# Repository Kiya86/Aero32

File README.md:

# Aero32

<h4 align="center">
A custom STM32N6-based AI vision module!
</h4>

<div align="center">

</div>

<p align="center">
  <a href="#key-features">Key Features</a> •
  <a href="#purpose">Purpose</a> •
  <a href="#pcb">PCB</a> •
  <a href="#main-components">Main Components</a> •
  <a href="#communication-interfaces">Communication Interfaces</a> •
  <a href="#power-architecture">Power System</a> •
  <a href="#bom">BOM</a> 
</p>

## Key Features

- **STM32N657X0H3Q** - Neural-ART accelerator that is used alongside the STM32N6 MCU
- **15-Pin CSI FPC Connector** - Camera sensor interface
- **MT35XU256ABA1G12** - 256 Mbit Octal SPI NOR Flash for either firmware or data 
- **IS66WVO32M8DALL** - 256 Mbit PSRAM for working memory
- **2× UART Ports** - Serial breakout headers
- **2× I2C Ports** - Two-wire serial communication breakout headers
- **1× SPI Port** - High-speed peripheral interface breakout
- **48 MHz & 32.768 kHz Crystals** - System clock and low power RTC
- **XT30 Battery Input** - 3S–4S LiPo input
- **5× Status LEDs** - 3 green + 2 red for power and debug feedback
- **Input OR** - TPS2121 power multiplexer for safe dual-source power switching

## Purpose

Aero32 is a small and compact AI vision board designed to serve as a node for drones or other flight hardware. The board offloads computer vision and processing from the external processing, communicating the results over UART, I2C, or SPI.

The STM32N6's Neural Processing Unit (NPU) allows anomaly detection, human recognition, and other advanced recognition directly on the board without AI hardware or wifi.

## PCB

Designed in **KiCad** and manufactured through **JLCPCB** (soon). The board uses a **6-layer PCB stackup** to allow for a reduction of EMI and signal interference. 

### Schematic

## Main Components

| Category | Component | Description |
|---|---|---|
| Microcontroller | STM32N657X0H3Q | STM32N6 with NPU |
| NOR Flash | MT35XU256ABA1G12-0AUT | 256 Mbit Octal SPI Flash (Micron) |
| PSRAM | IS66WVO32M8DALL-200BLI | 256 Mbit Pseudo-SRAM (ISSI) |
| Camera Connector | XF3M(1)-1515-1B | 15-Pin 1mm Pitch FPC (Omron) |
| Main Buck Regulator | LM61495Q5RPHRQ1 | 3–36V 10A Automotive Buck (TI) |
| Aux Buck (3A) | AP3441LSHE-7B | 2.7–5.5V 3A Adjustable Buck |
| Aux Buck (3A) | TPS62088YFPR | 2.4–5.5V 3A Adjustable Buck (TI) |
| Fixed 3.3V Buck | TPS560430X3FDBVR | 4–36V 600mA 3.3V Fixed Buck (TI) |
| 1.8V LDO (×2) | ETA5055V180DD1E | 1.8V 500mA LDO |
| 3.3V LDO | ETA5055V330DD1E | 3.3V 500mA LDO |
| Power Mux | TPS2121RUXR | ORing Power Multiplexer (TI) |
| USB ESD | TPD2E001DRYR | 2-Channel USB ESD Protection (TI) |
| USB Connector | HC-TYPE-C-16P-01A-G | USB Type-C 16P 3A Female |
| Power Input | XT30PW-M | XT30 Male 15A Connector |
| System Crystal | SX0B48.000F0810F30 | 48 MHz ±10ppm Crystal |
| RTC Crystal | NX2012SA 32.768K | 32.768 kHz ±20ppm Crystal |
| Boot / Reset | K2-1808SN-A4SW | SPST Tactile Switch (×2) |
| Status LEDs | KT-0603G / KT-0603R | Green (×3) / Red (×2) 0603 LEDs |
| TVS Diode | LESD5D5.0CT1G | 150W Bidirectional TVS 5V |

## Communication Interfaces

### UART (×2)
Two independent UART breakout ports via 2-pin JST ZH 1.5mm connectors.

### I2C (×2)
Two I2C ports broken out via JST ZH 1.5mm connectors.

### SPI (×1)
One SPI port available for high-speed peripheral communication.

### Camera (CSI)
A 15-pin 1mm pitch FPC connector (Omron XF3M) provides the camera sensor interface.

## Power Architecture

Aero32 supports dual power inputs (USB-C and XT30 battery) with automatic source switching via the TPS2121 power mux.

## BOM

The full Bill of Materials is available in [`Aero32_BOM.csv`](./PCB/Aero32_BOM.csv), formatted for direct JLCPCB assembly upload.

JLCPCB Quote

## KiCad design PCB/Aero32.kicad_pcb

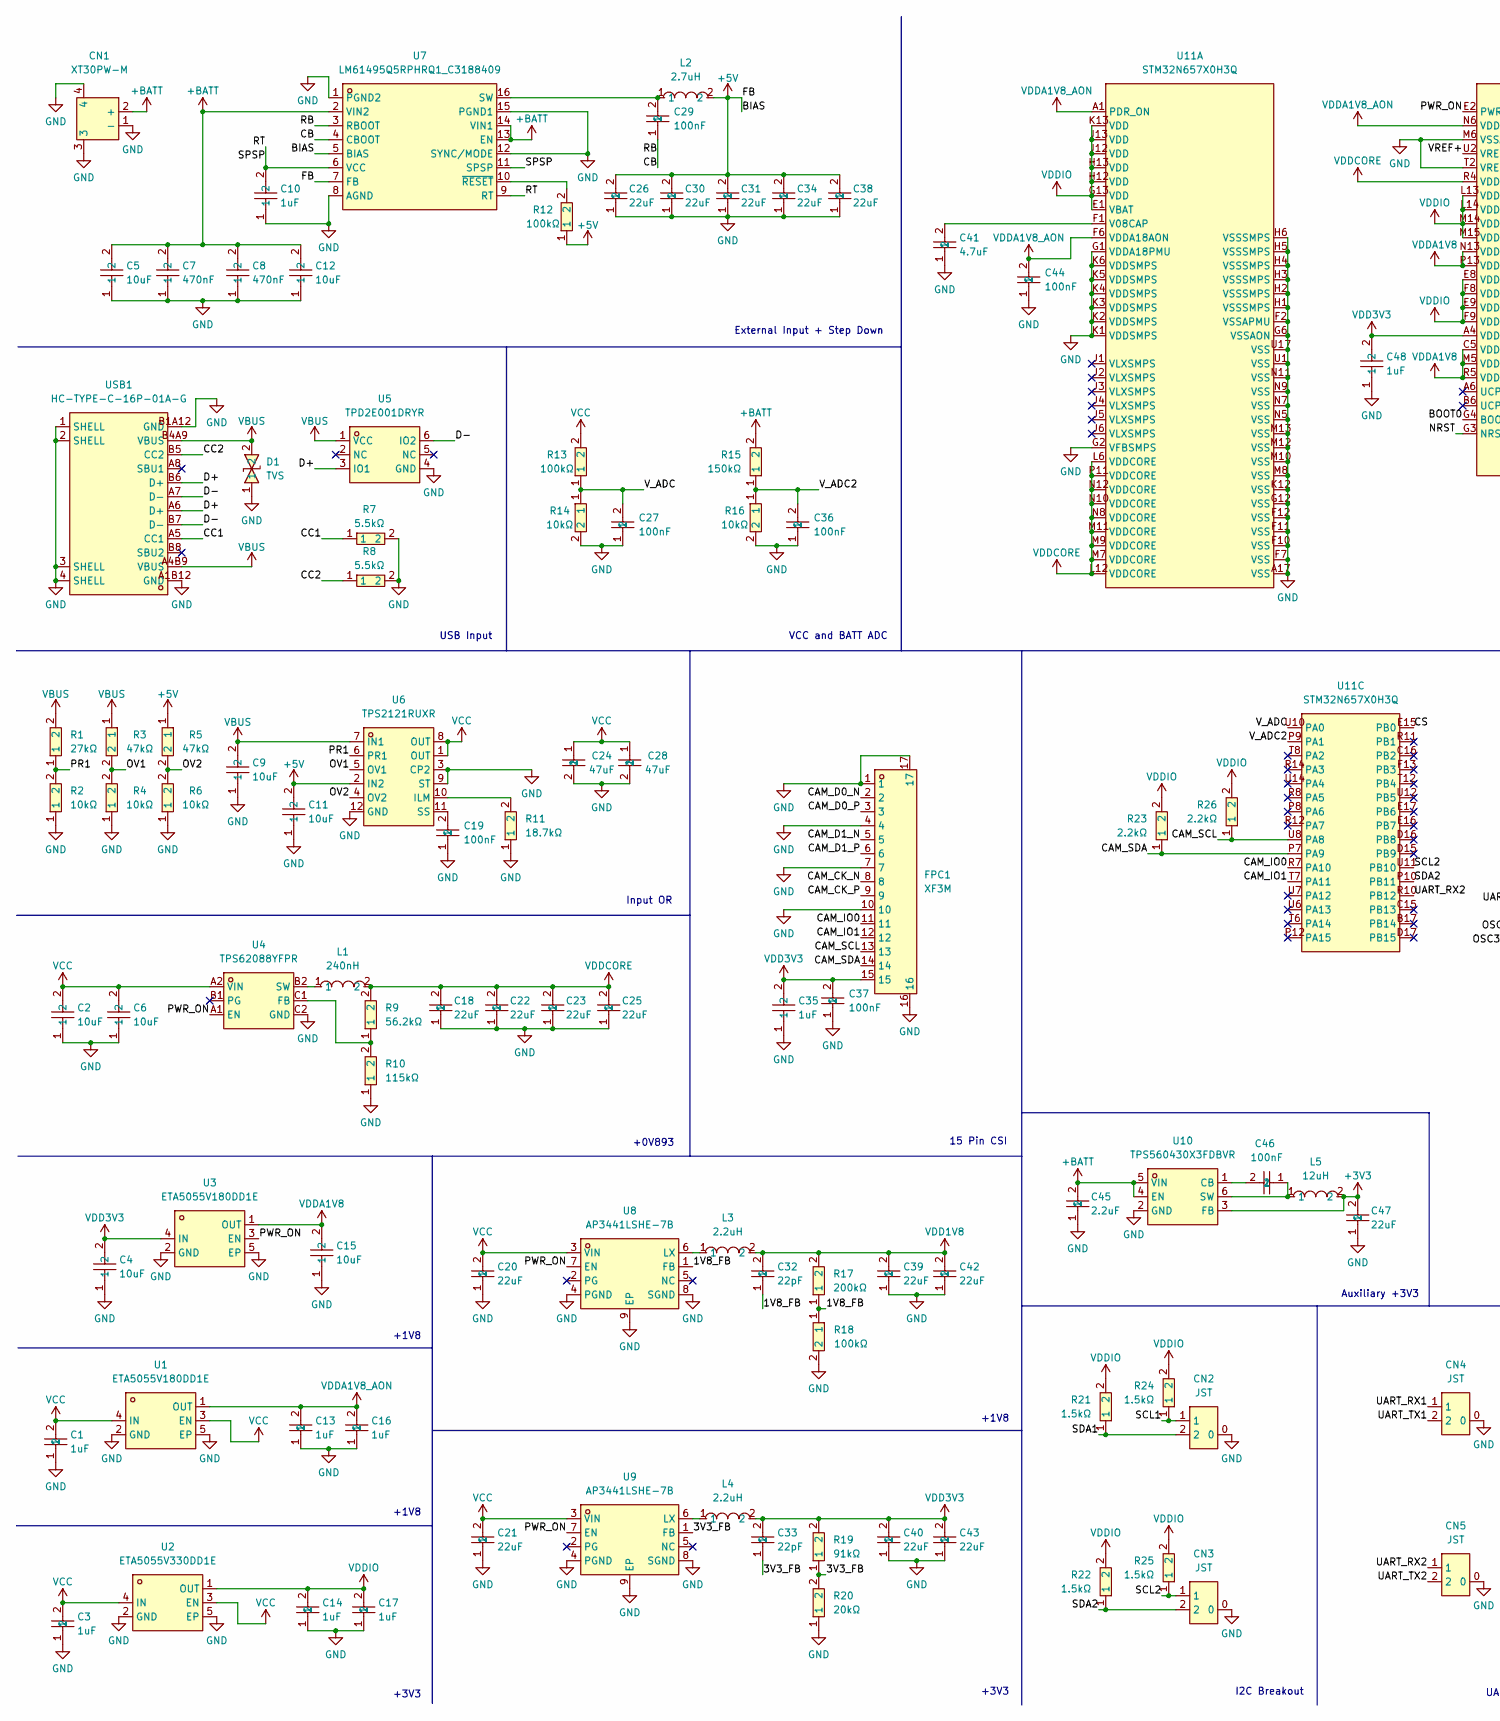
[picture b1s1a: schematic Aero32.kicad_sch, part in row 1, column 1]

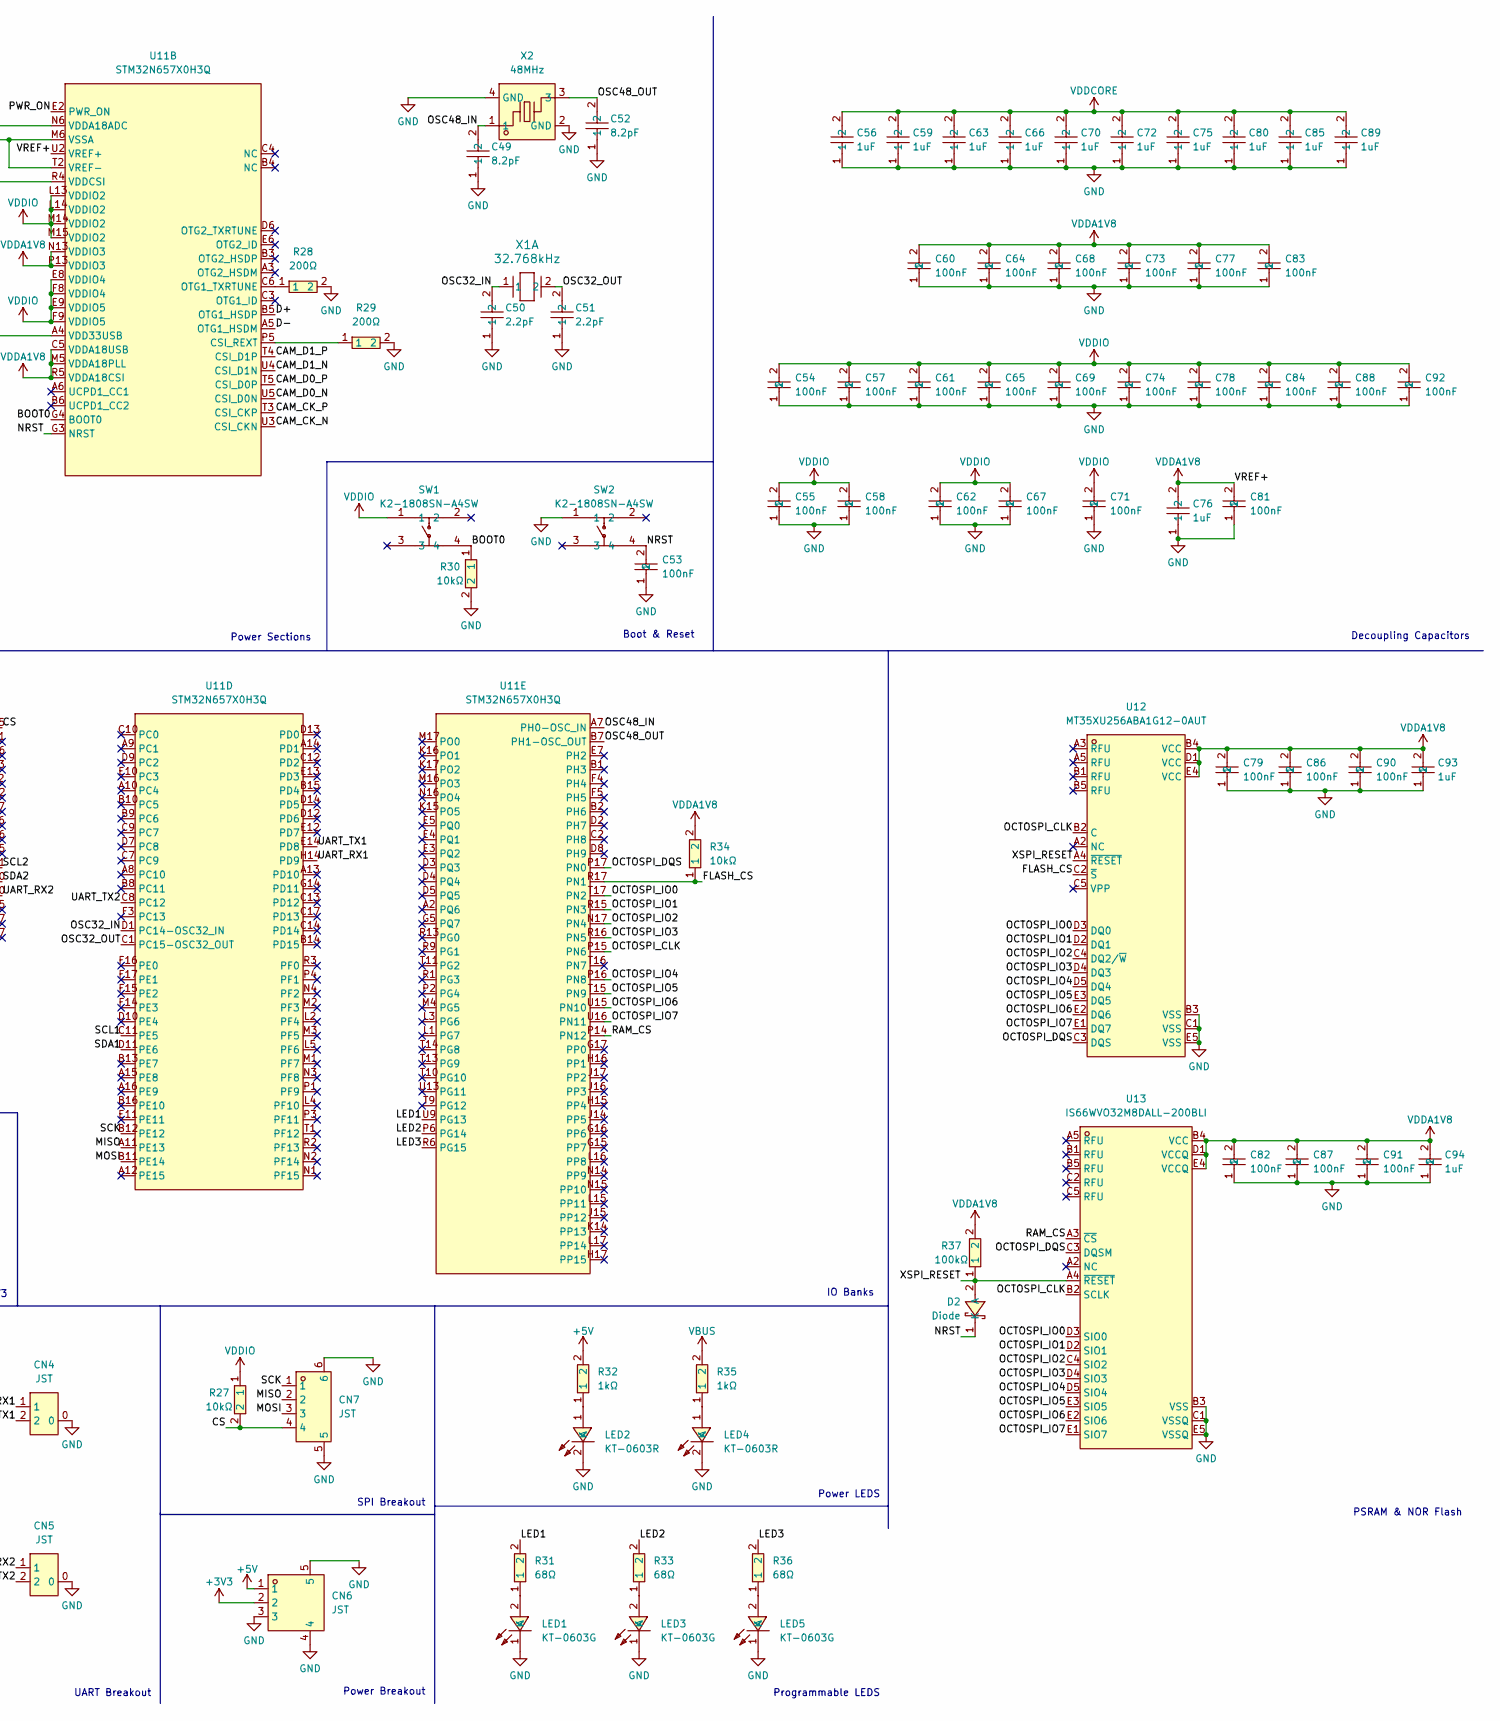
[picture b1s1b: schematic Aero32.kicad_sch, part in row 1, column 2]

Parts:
C1, C3, C13, C14, C16, C17, C93, C94: 1uF; C0603; MPN CL10A105KO8NNNC; LCSC Part C1592
C2, C4, C5, C6, C9, C11, C12, C15: 10uF; C0805; MPN GRM21BR61H106KE43L; LCSC Part C440198
C7, C8: 470nF; C0603; MPN CC0603KRX7R9BB474; LCSC Part C513577
C10, C35, C48, C56, C59, C63, C66, C70, C72, C75, C76, C80, C85, C89: 1uF; C0603; MPN CL10A105KB8NNNC; LCSC Part C15849
C18, C20, C21, C22, C23, C25, C26, C30, C31, C34, C38, C39, C40, C42, C43, C47: 22uF; C0805; MPN C2012X5R1A226KT000N; LCSC Part C76634
C19, C27, C29, C36, C37, C44, C46, C53, C54, C55, C57, C58, C60, C61, C62, C64, C65, C67, C68, C69, C71, C73, C74, C77, C78, C79, C81, C82, C83, C84, C86, C87, C88, C90, C91, C92: 100nF; C0603; MPN GRM188R71C104KA01D; LCSC Part C45000
C24, C28: 47uF; C1210; MPN GRM32ER71A476KE15L; LCSC Part C84494
C32, C33: 22pF; C0402; MPN 0402CG220J500NT; LCSC Part C1555
C41: 4.7uF; C0603; MPN CL10A475KP8NNNC; LCSC Part C1705
C45: 2.2uF; C0603; MPN CL10A225KP8NNNC; LCSC Part C1607
C49, C52: 8.2pF; C0402; MPN CC0402CRNPO9BN8R2; LCSC Part C260529
C50, C51: 2.2pF; C0402; MPN GJM1555C1H2R2WB01D; LCSC Part C88887
CN1: XT30PW-M; CONN-TH_XT30PW-M; MPN XT30PW-M30.G.Y; LCSC Part C431092
CN2, CN3, CN4, CN5: JST; CONN-SMD_S2B-ZR-SM4A; MPN S2B-ZR-SM4A-TF(LF)(SN); LCSC Part C265329
CN6: JST; CONN-TH_S3B-ZR-SM4A-TF-LF-SN; MPN S3B-ZR-SM4A-TF(LF)(SN); LCSC Part C72591
CN7: JST; CONN-SMD_4P-P1.50_S4B-ZR-SM4A-TF-LF-SN; MPN S4B-ZR-SM4A-TF(LF)(SN); LCSC Part C485354
D1: TVS; SOD-523_L1.2-W0.8-LS1.6-BI; MPN LESD5D5.0CT1G; LCSC Part C383211
D2: Diode; DSN2_L1.0-W0.6-RD; MPN NSR05F30NXT5G; LCSC Part C604339
FPC1: XF3M; FPC-SMD_XF3M-1-1515-1B; MPN XF3M(1)-1515-1B; LCSC Part C6036307
L1: 240nH; IND-SMD_L3.0-W3.0_MAI3015S; MPN MAI3015S-R24MT; LCSC Part C520265
L2: 2.7uH; IND-SMD_DH0630H-1R5M; MPN DH0630H-2R7M; LCSC Part C41407066
L3, L4: 2.2uH; IND-SMD_L4.5-W4.1_GSSM0420; MPN SL0420-2R2M; LCSC Part C22463806
L5: 12uH; IND-SMD_L4.8-W4.8; MPN LPS5030-123MRC; LCSC Part C22385343
LED1, LED3, LED5: KT-0603G; LED0603-RD; MPN KT-0603G; LCSC Part C12624
LED2, LED4: KT-0603R; LED-SMD_L1.6-W0.8-R-RD; MPN KT-0603R; LCSC Part C2286
R1: 27kΩ; R0603; MPN 0603WAF2702T5E; LCSC Part C22967
R2, R4, R6, R34: 10kΩ; R0603; MPN 0603WAF1002T5E; LCSC Part C25804
R3, R5: 47kΩ; R0603; MPN 0603WAF4702T5E; LCSC Part C25819
R7, R8: 5.5kΩ; R0805; MPN RMC08055.1K1%N; LCSC Part C269748
R9: 56.2kΩ; R0603; MPN 0603WAF5622T5E; LCSC Part C23080
R10: 115kΩ; R0603; MPN 0603WAF1153T5E; LCSC Part C22783
R11: 18.7kΩ; R0603; MPN 0603WAF1872T5E; LCSC Part C22893
R12, R13, R18, R37: 100kΩ; R0603; MPN RC0603FR-07100KL; LCSC Part C14675
R14, R16, R27, R30: 10kΩ; R0603; MPN 0603WAJ0103T5E; LCSC Part C15401
R15: 150kΩ; R0603; MPN 0603WAF1503T5E; LCSC Part C22807
R17: 200kΩ; R0603; MPN 0603WAF2003T5E; LCSC Part C25811
R19: 91kΩ; R0603; MPN 0603WAF9102T5E; LCSC Part C23265
R20: 20kΩ; R0603; MPN 0603WAF2002T5E; LCSC Part C4184
R21, R22, R24, R25: 1.5kΩ; R0402; MPN 0402WGF1501TCE; LCSC Part C25867
R23, R26: 2.2kΩ; R0402; MPN 0402WGF2201TCE; LCSC Part C25879
R28, R29: 200Ω; R0603; MPN 0603WAF2000T5E; LCSC Part C8218
R31, R33, R36: 68Ω; R0402; MPN 0402WGJ0680TCE; LCSC Part C25178
R32, R35: 1kΩ; R0402; MPN 0402WGF1001TCE; LCSC Part C11702
SW1, SW2: K2-1808SN-A4SW; KEY-SMD_4P-L4.2-W3.2-P2.20-LS5.1-TL; MPN K2-1808SN-A4SW-01; LCSC Part C92589
U1, U3: ETA5055V180DD1E; DFN-4_L1.0-W1.0-P0.65-BL-EP; MPN ETA5055V180DD1E; LCSC Part C5776774
U2: ETA5055V330DD1E; XDFN-4_L1.0-W1.0-P0.65-BL-EP; MPN ETA5055V330DD1E; LCSC Part C22466949
U4: TPS62088YFPR; DSBGA-6_L0.8-W1.2-P0.40-R3-C2-TL; MPN TPS62088YFPR; LCSC Part C575572
U5: TPD2E001DRYR; SON-6_L1.5-W1.0-P0.50-BL; MPN TPD2E001DRYR; LCSC Part C379992
U6: TPS2121RUXR; VQFN-HR-12_L2.5-W2.0-P0.50-BL; MPN TPS2121RUXR; LCSC Part C485916
U7: LM61495Q5RPHRQ1_C3188409; VQFN-16_L4.5-W3.5-P0.50-TL_TI_RPH; MPN LM61495Q5RPHRQ1; LCSC Part C3188409
U8, U9: AP3441LSHE-7B; DFN-8_L2.0-W2.0-P0.50-BL-EP1.7; MPN AP3441LSHE-7B; LCSC Part C2072094
U10: TPS560430X3FDBVR; SOT-23-6_L2.9-W1.6-P0.95-LS2.8-BR; MPN TPS560430X3FDBVR; LCSC Part C2071721
U11: STM32N657X0H3Q; BGA-264_L14.0-W14.0-STM32N657X0H3Q; MPN STM32N657X0H3Q; LCSC Part C42418080
U12: MT35XU256ABA1G12-0AUT; T-PBGA-24_L8.0-W6.0-P1.00-TL_MICRON_12; MPN MT35XU256ABA1G12-0AUT; LCSC Part C7235747
U13: IS66WVO32M8DALL-200BLI; TFBGA-24_L8.0-W6.0-P1.00-TL_MX25UW25645GXDI00; MPN IS66WVO32M8DALL-200BLI; LCSC Part C17535354
USB1: HC-TYPE-C-16P-01A-G; USB-C-SMD_G-SWITCH_GT-USB-7010EN; MPN HC-TYPE-C-16P-01A-G; LCSC Part C2997435
X1: 32.768kHz; XTAL_NX2012SA_NDK
X2: 48MHz; CRYSTAL-SMD_4P-L1.6-W1.2-BL; MPN SX0B48.000F0810F30; LCSC Part C7301928

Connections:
+3V3: C47.2, CN6.2, L5.2, U10.3 (FB)
+5V: C11.2, C26.2, C30.2, C31.2, C34.2, C38.2, CN6.1, L2.2, R5.1, R12.1, R32.2, U6.2 (IN2), U7.5 (BIAS), U7.7 (FB)
+BATT: C5.2, C7.2, C8.2, C12.2, C45.2, CN1.2 (+), R15.2, U7.2 (VIN2), U7.13 (EN), U7.14 (VIN1), U10.4 (EN), U10.5 (VIN)
/3V3_FB: C33.1, R19.1, R20.2, U9.1 (FB)
/BOOT0: R30.1, SW1.4, U11.G4 (BOOT0)
/CAM_CK_N: FPC1.8, U11.U3 (CSI_CKN)
/CAM_CK_P: FPC1.9, U11.T3 (CSI_CKP)
/CAM_D0_N: FPC1.2, U11.U5 (CSI_D0N)
/CAM_D0_P: FPC1.3, U11.T5 (CSI_D0P)
/CAM_D1_N: FPC1.5, U11.U4 (CSI_D1N)
/CAM_D1_P: FPC1.6, U11.T4 (CSI_D1P)
/CAM_IO0: FPC1.11, U11.R7 (PA10)
/CAM_IO1: FPC1.12, U11.T7 (PA11)
/CAM_SCL: FPC1.13, R26.1, U11.U8 (PA8)
/CAM_SDA: FPC1.14, R23.1, U11.P7 (PA9)
/CB: C29.1, U7.3 (RBOOT), U7.4 (CBOOT)
/CC1: R7.1, USB1.A5 (CC1)
/CC2: R8.1, USB1.B5 (CC2)
/CS: CN7.4, R27.2, U11.E15 (PB0)
/D+: U5.3 (IO1), U11.B5 (OTG1_HSDP), USB1.A6 (D+), USB1.B6 (D+)
/D-: U5.6 (IO2), U11.A5 (OTG1_HSDM), USB1.A7 (D-), USB1.B7 (D-)
/FLASH_CS: R34.1, U11.R17 (PN1), U12.C2 (~S)
/LED1: R31.2, U11.U9 (PG13)
/LED2: R33.2, U11.P6 (PG14)
/LED3: R36.2, U11.R6 (PG15)
/MISO: CN7.2, U11.A11 (PE13)
/MOSI: CN7.3, U11.B11 (PE14)
/NRST: C53.2, D2.1 (K), SW2.4, U11.G3 (NRST)
/OCTOSPI_CLK: U11.P15 (PN6), U12.B2 (C), U13.B2 (SCLK)
/OCTOSPI_DQS: U11.P17 (PN0), U12.C3 (DQS), U13.C3 (DQSM)
/OCTOSPI_IO0: U11.T17 (PN2), U12.D3 (DQ0), U13.D3 (SIO0)
/OCTOSPI_IO1: U11.R15 (PN3), U12.D2 (DQ1), U13.D2 (SIO1)
/OCTOSPI_IO2: U11.N17 (PN4), U12.C4 (DQ2/~W), U13.C4 (SIO2)
/OCTOSPI_IO3: U11.R16 (PN5), U12.D4 (DQ3), U13.D4 (SIO3)
/OCTOSPI_IO4: U11.P16 (PN8), U12.D5 (DQ4), U13.D5 (SIO4)
/OCTOSPI_IO5: U11.T15 (PN9), U12.E3 (DQ5), U13.E3 (SIO5)
/OCTOSPI_IO6: U11.U15 (PN10), U12.E2 (DQ6), U13.E2 (SIO6)
/OCTOSPI_IO7: U11.U16 (PN11), U12.E1 (DQ7), U13.E1 (SIO7)
/OSC32_IN: C50.2, U11.D1 (PC14-OSC32_IN), X1.1
/OSC32_OUT: C51.2, U11.C1 (PC15-OSC32_OUT), X1.2
/OSC48_IN: C49.2, U11.A7 (PH0-OSC_IN), X2.1
/OSC48_OUT: C52.2, U11.B7 (PH1-OSC_OUT), X2.3
/OV1: R3.2, R4.2, U6.5 (OV1)
/OV2: R5.2, R6.2, U6.4 (OV2)
/PR1: R1.1, R2.2, U6.6 (PR1)
/PWR_ON: U3.3 (EN), U4.A1 (EN), U8.7 (EN), U9.7 (EN), U11.E2 (PWR_ON)
/RAM_CS: U11.P14 (PN12), U13.A3 (~CS)
/RT: C10.2, U7.6 (VCC), U7.9 (RT), U7.11 (SPSP)
/SCK: CN7.1, U11.B12 (PE12)
/SCL1: CN2.1, R24.1, U11.C11 (PE5)
/SCL2: CN3.1, R25.1, U11.U11 (PB10)
/SDA1: CN2.2, R21.1, U11.D11 (PE6)
/SDA2: CN3.2, R22.1, U11.P10 (PB11)
/UART_RX1: CN4.1, U11.H14 (PD9)
/UART_RX2: CN5.1, U11.R10 (PB12)
/UART_TX1: CN4.2, U11.E14 (PD8)
/UART_TX2: CN5.2, U11.C8 (PC12)
/V_ADC: C27.2, R13.1, R14.1, U11.U10 (PA0)
/V_ADC2: C36.2, R15.1, R16.1, U11.P9 (PA1)
/XSPI_RESET: D2.2 (A), R37.1, U12.A4 (~RESET), U13.A4 (~RESET)
GND: C1.1, C2.1, C3.1, C4.1, C5.1, C6.1, C7.1, C8.1, C9.1, C10.1, C11.1, C12.1, C13.1, C14.1, C15.1, C16.1, C17.1, C18.1, C19.1, C20.1, C21.1, C22.1, C23.1, C24.2, C25.1, C26.1, C27.1, C28.2, C30.1, C31.1, C34.1, C35.1, C36.1, C37.1, C38.1, C39.1, C40.1, C41.1, C42.1, C43.1, C44.1, C45.1, C47.1, C48.1, C49.1, C50.1, C51.1, C52.1, C53.1, C54.1, C55.1, C56.1, C57.1, C58.1, C59.1, C60.1, C61.1, C62.1, C63.1, C64.1, C65.1, C66.1, C67.1, C68.1, C69.1, C70.1, C71.1, C72.1, C73.1, C74.1, C75.1, C76.1, C77.1, C78.1, C79.1, C80.1, C81.1, C82.1, C83.1, C84.1, C85.1, C86.1, C87.1, C88.1, C89.1, C90.1, C91.1, C92.1, C93.1, C94.1, CN1.1 (-), CN1.3, CN1.4, CN2.0, CN3.0, CN4.0, CN5.0, CN6.3, CN6.4, CN6.5, CN7.5, CN7.6, D1.1, FPC1.1, FPC1.4, FPC1.7, FPC1.10, FPC1.16, FPC1.17, LED1.1 (K), LED2.2 (K), LED3.1 (K), LED4.2 (K), LED5.1 (K), R2.1, R4.1, R6.1, R7.2, R8.2, R10.1, R11.1, R14.2, R16.2, R18.2, R20.1, R28.2, R29.2, R30.2, SW2.1, U1.2 (GND), U1.5 (EP), U2.2 (GND), U2.5 (EP), U3.2 (GND), U3.5 (EP), U4.C2 (GND), U5.4 (GND), U6.3 (CP2), U6.9 (ST), U6.12 (GND), U7.1 (PGND2), U7.8 (AGND), U7.12 (SYNC/MODE), U7.15 (PGND1), U8.4 (PGND), U8.8 (SGND), U8.9 (EP), U9.4 (PGND), U9.8 (SGND), U9.9 (EP), U10.2 (GND), U11.A17 (VSS), U11.F2 (VSSAPMU), U11.F7 (VSS), U11.F10 (VSS), U11.F11 (VSS), U11.F12 (VSS), U11.G1 (VDDA18PMU), U11.G2 (VFBSMPS), U11.G6 (VSSAON), U11.G12 (VSS), U11.H1 (VSSSMPS), U11.H2 (VSSSMPS), U11.H3 (VSSSMPS), U11.H4 (VSSSMPS), U11.H5 (VSSSMPS), U11.H6 (VSSSMPS), U11.K1 (VDDSMPS), U11.K2 (VDDSMPS), U11.K3 (VDDSMPS), U11.K4 (VDDSMPS), U11.K5 (VDDSMPS), U11.K6 (VDDSMPS), U11.K12 (VSS), U11.M6 (VSSA), U11.M8 (VSS), U11.M10 (VSS), U11.M12 (VSS), U11.M13 (VSS), U11.N5 (VSS), U11.N7 (VSS), U11.N9 (VSS), U11.N11 (VSS), U11.T2 (VREF-), U11.U1 (VSS), U11.U17 (VSS), U12.B3 (VSS), U12.C1 (VSS), U12.E5 (VSS), U13.B3 (VSS), U13.C1 (VSSQ), U13.E5 (VSSQ), USB1.1 (SHELL), USB1.2 (SHELL), USB1.3 (SHELL), USB1.4 (SHELL), USB1.A1B12 (GND), USB1.B1A12 (GND), X2.2 (GND), X2.4 (GND)
unnamed: C32.1, R17.1, R18.1, U8.1 (FB)
unnamed: C32.2, C39.2, C42.2, L3.2, R17.2
unnamed: L3.1, U8.6 (LX)
unnamed: LED1.2 (A), R31.1
unnamed: LED2.1 (A), R32.1
unnamed: LED3.2 (A), R33.1
unnamed: LED4.1 (A), R35.1
unnamed: LED5.2 (A), R36.1
unnamed: R9.1, R10.2, U4.C1 (FB)
unnamed: L1.1, U4.B2 (SW)
unnamed: R11.2, U6.10 (ILM)
unnamed: C19.2, U6.11 (SS)
unnamed: C29.2, L2.1, U7.16 (SW)
unnamed: R12.2, U7.10 (~RESET)
unnamed: L4.1, U9.6 (LX)
unnamed: C46.2, U10.1 (CB)
unnamed: C46.1, L5.1, U10.6 (SW)
unnamed: C41.2, U11.F1 (V08CAP)
unnamed: R29.1, U11.P5 (CSI_REXT)
unnamed: R28.1, U11.C6 (OTG1_TXRTUNE)
VBUS: C9.2, D1.2, R1.2, R3.1, R35.2, U5.1 (VCC), U6.7 (IN1), USB1.A4B9 (VBUS), USB1.B4A9 (VBUS)
VCC: C1.2, C2.2, C3.2, C6.2, C20.2, C21.2, C24.1, C28.1, R13.2, U1.3 (EN), U1.4 (IN), U2.3 (EN), U2.4 (IN), U4.A2 (VIN), U6.1 (OUT), U6.8 (OUT), U8.3 (VIN), U9.3 (VIN)
VDD3V3: C4.2, C33.2, C35.2, C37.2, C40.2, C43.2, C48.2, FPC1.15, L4.2, R19.2, U3.4 (IN), U11.A4 (VDD33USB)
VDDA1V8: C15.2, C60.2, C64.2, C68.2, C73.2, C76.2, C77.2, C79.2, C81.2, C82.2, C83.2, C86.2, C87.2, C90.2, C91.2, C93.2, C94.2, R34.2, R37.2, U3.1 (OUT), U11.C5 (VDDA18USB), U11.M5 (VDDA18PLL), U11.N13 (VDDIO3), U11.P13 (VDDIO3), U11.R5 (VDDA18CSI), U11.U2 (VREF+), U12.B4 (VCC), U12.D1 (VCC), U12.E4 (VCC), U13.B4 (VCC), U13.D1 (VCCQ), U13.E4 (VCCQ)
VDDA1V8_AON: C13.2, C16.2, C44.2, U1.1 (OUT), U11.A1 (PDR_ON), U11.F6 (VDDA18AON), U11.N6 (VDDA18ADC)
VDDCORE: C18.2, C22.2, C23.2, C25.2, C56.2, C59.2, C63.2, C66.2, C70.2, C72.2, C75.2, C80.2, C85.2, C89.2, L1.2, R9.2, U11.L6 (VDDCORE), U11.L12 (VDDCORE), U11.M7 (VDDCORE), U11.M9 (VDDCORE), U11.M11 (VDDCORE), U11.N8 (VDDCORE), U11.N10 (VDDCORE), U11.N12 (VDDCORE), U11.P11 (VDDCORE), U11.R4 (VDDCSI)
VDDIO: C14.2, C17.2, C54.2, C55.2, C57.2, C58.2, C61.2, C62.2, C65.2, C67.2, C69.2, C71.2, C74.2, C78.2, C84.2, C88.2, C92.2, R21.2, R22.2, R23.2, R24.2, R25.2, R26.2, R27.1, SW1.1, U2.1 (OUT), U11.E1 (VBAT), U11.E8 (VDDIO4), U11.E9 (VDDIO5), U11.F8 (VDDIO4), U11.F9 (VDDIO5), U11.G13 (VDD), U11.H12 (VDD), U11.H13 (VDD), U11.J12 (VDD), U11.J13 (VDD), U11.K13 (VDD), U11.L13 (VDDIO2), U11.L14 (VDDIO2), U11.M14 (VDDIO2), U11.M15 (VDDIO2)

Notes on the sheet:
+3V3
I2C Breakout
Power Sections
IO Banks
Input OR
Auxiliary +3V3
Power Breakout
UART Breakout
15 Pin CSI
USB Input
+1V8
External Input + Step Down
SPI Breakout
Power LEDS
PSRAM & NOR Flash
Programmable LEDS
+0V893
Decoupling Capacitors
VCC and BATT ADC
Boot & Reset

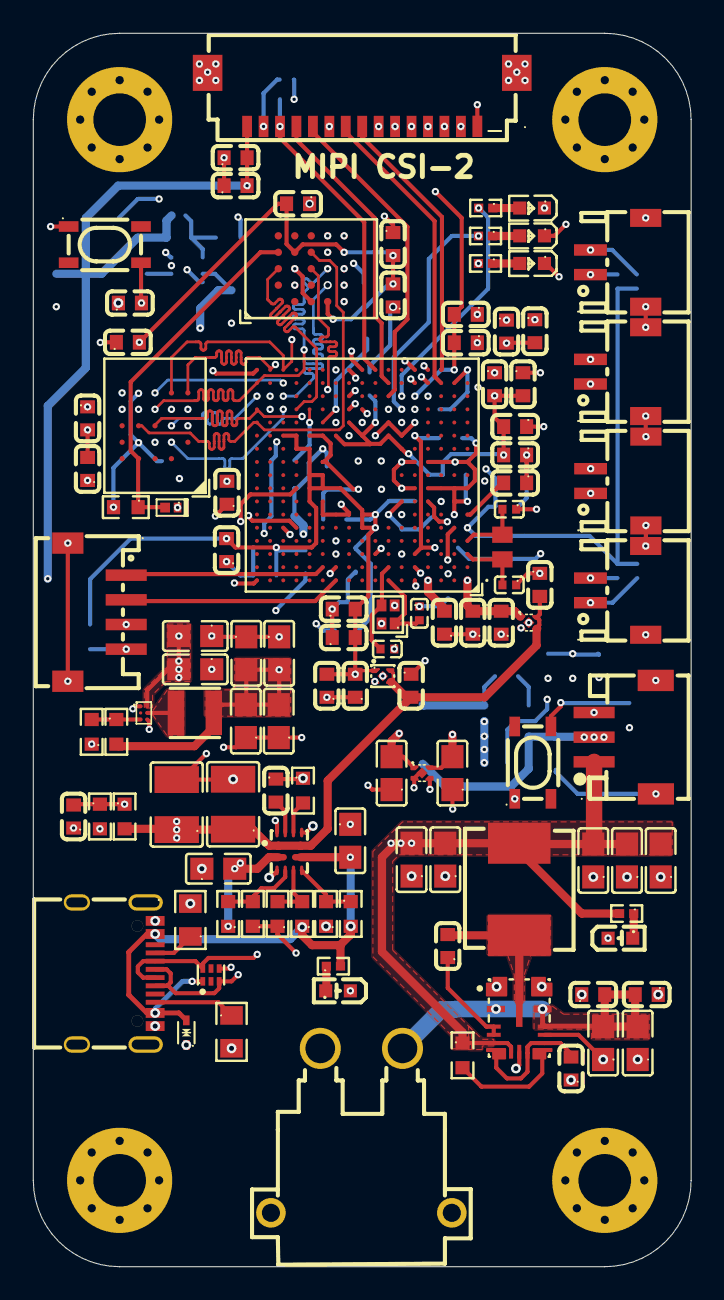
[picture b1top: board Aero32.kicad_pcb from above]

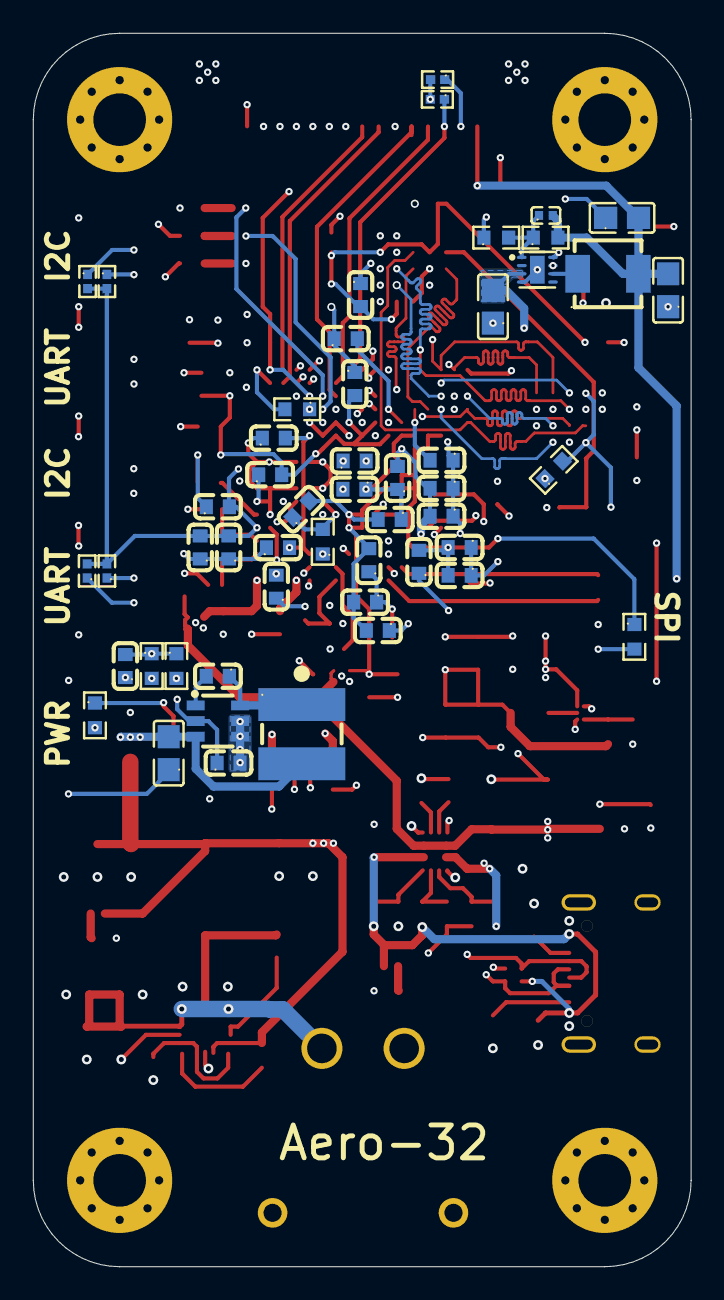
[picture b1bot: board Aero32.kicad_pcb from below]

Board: 6 copper layers, 40.0 x 75.0 mm, 161 parts (51 on the bottom side), 85 nets.

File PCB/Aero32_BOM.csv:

#,References,Value,Footprint,Qty,MFR Part #,JLCPCB #,Manufacturer,Description
1,"C19, C27, C29, C36, C37, C44, C46, C53, C54, C55, C57, C58, C60, C61, C62, C64, C65, C67, C68, C69, C71, C73, C74, C77, C78, C79, C81, C82, C83, C84, C86, C87, C88, C90, C91, C92",100nF,C0603,36,GRM188R71C104KA01D,C45000,Murata Electronics,100nF 16V X7R ±10% MLCC
2,"C1, C3, C10, C13, C14, C16, C17, C35, C48, C56, C59, C63, C66, C70, C72, C75, C76, C80, C85, C89, C93, C94",1uF,C0603,22,CL10A105KO8NNNC,C1592,Samsung Electro-Mechanics,16V 1uF X5R ±10% MLCC
3,"C18, C21, C22, C23, C25, C26, C30, C31, C34, C38, C40, C43, C47",22uF,C0805,13,C2012X5R1A226KT000N,C76634,TDK,10V 22uF X5R ±10% MLCC
4,"C2, C4, C5, C6, C9, C11, C12, C15",10uF,C0805,8,GRM21BR61H106KE43L,C440198,Murata Electronics,10uF 50V X5R ±10% MLCC
5,"C7, C8",470nF,C0603,2,CC0603KRX7R9BB474,C513577,YAGEO,470nF 50V X7R ±10% MLCC
6,"C24, C28",47uF,C1210,2,GRM32ER71A476KE15L,C84494,Murata Electronics,10V 47uF X7R ±10% MLCC
7,"C49, C52",8.2pF,C0402,2,CC0402CRNPO9BN8R2,C260529,YAGEO,50V 8.2pF NP0 MLCC
8,"C50, C51",2.2pF,C0402,2,GJM1555C1H2R2WB01D,C88887,Murata Electronics,2.2pF 50V C0G MLCC
9,C33,22pF,C0402,1,0402CG220J500NT,C1555,FH (Guangdong Fenghua),22pF 50V C0G ±5% MLCC
10,C41,4.7uF,C0603,1,CL10A475KP8NNNC,C1705,Samsung Electro-Mechanics,10V 4.7uF X5R ±10% MLCC
11,C45,2.2uF,C0603,1,CL10A225KP8NNNC,C1607,Samsung Electro-Mechanics,10V 2.2uF X5R ±10% MLCC
12,"R2, R4, R6, R34",10kΩ,R0603,4,0603WAF1002T5E,C25804,UNI-ROYAL,10kΩ ±1% 100mW Thick Film
13,"R14, R16, R27, R30",10kΩ,R0603,4,0603WAJ0103T5E,C25804,UNI-ROYAL,10kΩ ±1% 100mW Thick Film
14,"R21, R22, R24, R25",1.5kΩ,R0402,4,0402WGF1501TCE,C25867,UNI-ROYAL,1.5kΩ ±1% 62.5mW Thick Film
15,"R12, R13, R37",100kΩ,R0603,3,RC0603FR-07100KL,C14675,YAGEO,100kΩ ±1% 100mW Thick Film
16,"R31, R33, R36",68Ω,R0402,3,0402WGJ0680TCE,C25178,UNI-ROYAL,68Ω ±5% 62.5mW Thick Film
17,"R3, R5",47kΩ,R0603,2,0603WAF4702T5E,C25819,UNI-ROYAL,47kΩ ±1% 100mW Thick Film
18,"R7, R8",5.1kΩ,R0805,2,RMC08055.1K1%N,C269748,TyoHM,5.1kΩ ±1% 125mW Thick Film
19,"R23, R26",2.2kΩ,R0402,2,0402WGF2201TCE,C25879,UNI-ROYAL,2.2kΩ ±1% 62.5mW Thick Film
20,"R28, R29",200Ω,R0603,2,0603WAF2000T5E,C8218,UNI-ROYAL,200Ω ±1% 100mW Thick Film
21,"R32, R35",1kΩ,R0402,2,0402WGF1001TCE,C11702,UNI-ROYAL,1kΩ ±1% 62.5mW Thick Film
22,R1,27kΩ,R0603,1,0603WAF2702T5E,C22967,UNI-ROYAL,27kΩ ±1% 100mW Thick Film
23,R9,56.2kΩ,R0603,1,0603WAF5622T5E,C23080,UNI-ROYAL,56.2kΩ ±1% 100mW Thick Film
24,R10,115kΩ,R0603,1,0603WAF1153T5E,C22783,UNI-ROYAL,115kΩ ±1% 100mW Thick Film
25,R11,18.7kΩ,R0603,1,0603WAF1872T5E,C22893,UNI-ROYAL,18.7kΩ ±1% 100mW Thick Film
26,R15,150kΩ,R0603,1,0603WAF1503T5E,C22807,UNI-ROYAL,150kΩ ±1% 100mW Thick Film
27,R19,91kΩ,R0603,1,0603WAF9102T5E,C23265,UNI-ROYAL,91kΩ ±1% 100mW Thick Film
28,R20,20kΩ,R0603,1,0603WAF2002T5E,C4184,UNI-ROYAL,20kΩ ±1% 100mW Thick Film
29,L1,240nH,IND-SMD_L3.0-W3.0_MAI3015S,1,MAI3015S-R24MT,C520265,Ceaiya,240nH 5A Power Inductor
30,L2,2.7uH,IND-SMD_DH0630H-1R5M,1,DH0630H-2R7M,C41407066,dehongganying,2.7uH 12A Power Inductor
31,L4,2.2uH,IND-SMD_L4.5-W4.1_GSSM0420,1,SL0420-2R2M,C22463806,TECHFUSE,2.2uH 4.5A Inductor
32,L5,12uH,IND-SMD_L4.8-W4.8,1,LPS5030-123MRC,C22385343,Coilcraft,12uH 1.4A Shielded Power Inductor
33,D1,TVS,SOD-523_L1.2-W0.8-LS1.6-BI,1,LESD5D5.0CT1G,C383211,LRC,150W Bidirectional TVS 5V SOD-523
34,D2,Diode,DSN2_L1.0-W0.6-RD,1,NSR05F30NXT5G,C604339,onsemi,Schottky Diode 30V 500mA
35,"U1, U3",ETA5055V180DD1E,DFN-4_L1.0-W1.0-P0.65-BL-EP,2,ETA5055V180DD1E,C5776774,etasolution,1.8V 500mA LDO Regulator
36,U2,ETA5055V330DD1E,XDFN-4_L1.0-W1.0-P0.65-BL-EP,1,ETA5055V330DD1E,C22466949,etasolution,3.3V 500mA LDO Regulator
37,U4,TPS62088YFPR,DSBGA-6_L0.8-W1.2-P0.40-R3-C2-TL,1,TPS62088YFPR,C575572,Texas Instruments,2.4–5.5V 3A Adjustable Buck
38,U5,TPD2E001DRYR,SON-6_L1.5-W1.0-P0.50-BL,1,TPD2E001DRYR,C379992,Texas Instruments,USB ESD Protection 2-ch
39,U6,TPS2121RUXR,VQFN-HR-12_L2.5-W2.0-P0.50-BL,1,TPS2121RUXR,C485916,Texas Instruments,ORing Power Mux Controller
40,U7,LM61495Q5RPHRQ1_C3188409,VQFN-16_L4.5-W3.5-P0.50-TL_TI_RPH,1,LM61495Q5RPHRQ1,C3188409,Texas Instruments,3–36V 10A Automotive Buck
41,U9,AP3441LSHE-7B,DFN-8_L2.0-W2.0-P0.50-BL-EP1.7,1,AP3441LSHE-7B,C2072094,Diodes Incorporated,2.7–5.5V 3A Adjustable Buck
42,U10,TPS560430X3FDBVR,SOT-23-6_L2.9-W1.6-P0.95-LS2.8-BR,1,TPS560430X3FDBVR,C2071721,Texas Instruments,4–36V 600mA 3.3V Fixed Buck
43,U11,STM32N657X0H3Q,BGA-264_L14.0-W14.0-STM32N657X0H3Q,1,STM32N657X0H3Q,C42418080,STMicroelectronics,STM32N6 MCU BGA-264
44,U12,MT35XU256ABA1G12-0AUT,T-PBGA-24_L8.0-W6.0-P1.00-TL_MICRON_12,1,MT35XU256ABA1G12-0AUT,C7235747,Micron Tech,256Mbit Octal SPI NOR Flash
45,U13,IS66WVO32M8DALL-200BLI,TFBGA-24_L8.0-W6.0-P1.00-TL_MX25UW25645GXDI00,1,IS66WVO32M8DALL-200BLI,C17535354,ISSI,256Mbit PSRAM
46,X1,32.768kHz,XTAL_NX2012SA_NDK,1,NX2012SA_32.768K_STD-MUB-1,C500343,NDK,32.768kHz Crystal ±20ppm
47,X2,48MHz,CRYSTAL-SMD_4P-L1.6-W1.2-BL,1,SX0B48.000F0810F30,C7301928,Shenzhen SCTF Elec,48MHz Crystal ±10ppm
48,"SW1, SW2",K2-1808SN-A4SW,KEY-SMD_4P-L4.2-W3.2-P2.20-LS5.1-TL,2,K2-1808SN-A4SW-01,C92589,Korean Hroparts Elec,SPST Tactile Switch 12V 50mA
49,"CN2, CN3, CN4, CN5",JST,CONN-SMD_S2B-ZR-SM4A,4,S2B-ZR-SM4A-TF(LF)(SN),C265329,JST,2-Pin ZH 1.5mm SMD Connector
50,"LED1, LED3, LED5",KT-0603G,LED0603-RD,3,KT-0603G,C12624,Hubei KENTO Elec,Green LED 525nm 0603
51,"LED2, LED4",KT-0603R,LED-SMD_L1.6-W0.8-R-RD,2,KT-0603R,C2286,Hubei KENTO Elec,Red LED 645nm 0603
52,CN1,XT30PW-M,CONN-TH_XT30PW-M,1,XT30PW-M30.G.Y,C431092,Changzhou Amass Elec,XT30 Male Power Connector 15A
53,CN6,JST,CONN-TH_S3B-ZR-SM4A-TF-LF-SN,1,S3B-ZR-SM4A-TF(LF)(SN),C72591,JST,3-Pin ZH 1.5mm SMD Connector
54,CN7,JST,CONN-SMD_4P-P1.50_S4B-ZR-SM4A-TF-LF-SN,1,S4B-ZR-SM4A-TF(LF)(SN),C485354,JST,4-Pin ZH 1.5mm SMD Connector
55,FPC1,XF3M,FPC-SMD_XF3M-1-1515-1B,1,XF3M(1)-1515-1B,C6036307,Omron Electronics,15P 1mm Pitch FPC Connector
56,USB1,HC-TYPE-C-16P-01A-G,USB-C-SMD_G-SWITCH_GT-USB-7010EN,1,HC-TYPE-C-16P-01A-G,C2997435,HCTL,USB Type-C 16P 3A Female

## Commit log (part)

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2026-06-26 Create s
